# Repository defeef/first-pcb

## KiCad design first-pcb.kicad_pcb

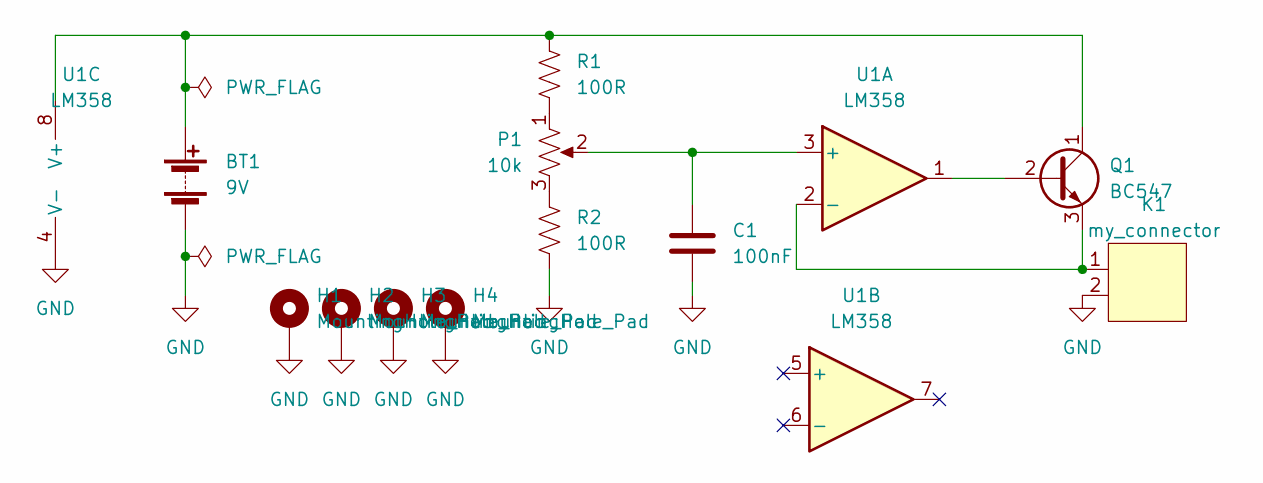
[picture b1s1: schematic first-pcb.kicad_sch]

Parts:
BT1: 9V; BatteryHolder_Eagle_12BH611-GR
C1: 100nF; C_Disc_D3.0mm_W2.0mm_P2.50mm
H1, H2, H3, H4: MountingHole_Pad; MountingHole_3.2mm_M3_Pad
K1: my_connector; PinHeader_1x02_P2.54mm_Vertical
P1: 10k; Potentiometer_Alps_RK09K_Single_Vertical
Q1: BC547; TO-92_Inline
R1, R2: 100R; R_Axial_DIN0207_L6.3mm_D2.5mm_P10.16mm_Horizontal
U1: LM358; DIP-8_W7.62mm

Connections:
GND: BT1.2 (-), C1.2, H1.1, H2.1, H3.1, H4.1, K1.2, R2.2, U1.4 (V-)
unnamed: BT1.1 (+), Q1.1 (C), R1.1, U1.8 (V+)
unnamed: C1.1, P1.2, U1.3 (+)
unnamed: K1.1, Q1.3 (E), U1.2 (-)
unnamed: P1.1, R1.2
unnamed: P1.3, R2.1
unnamed: Q1.2 (B), U1.1

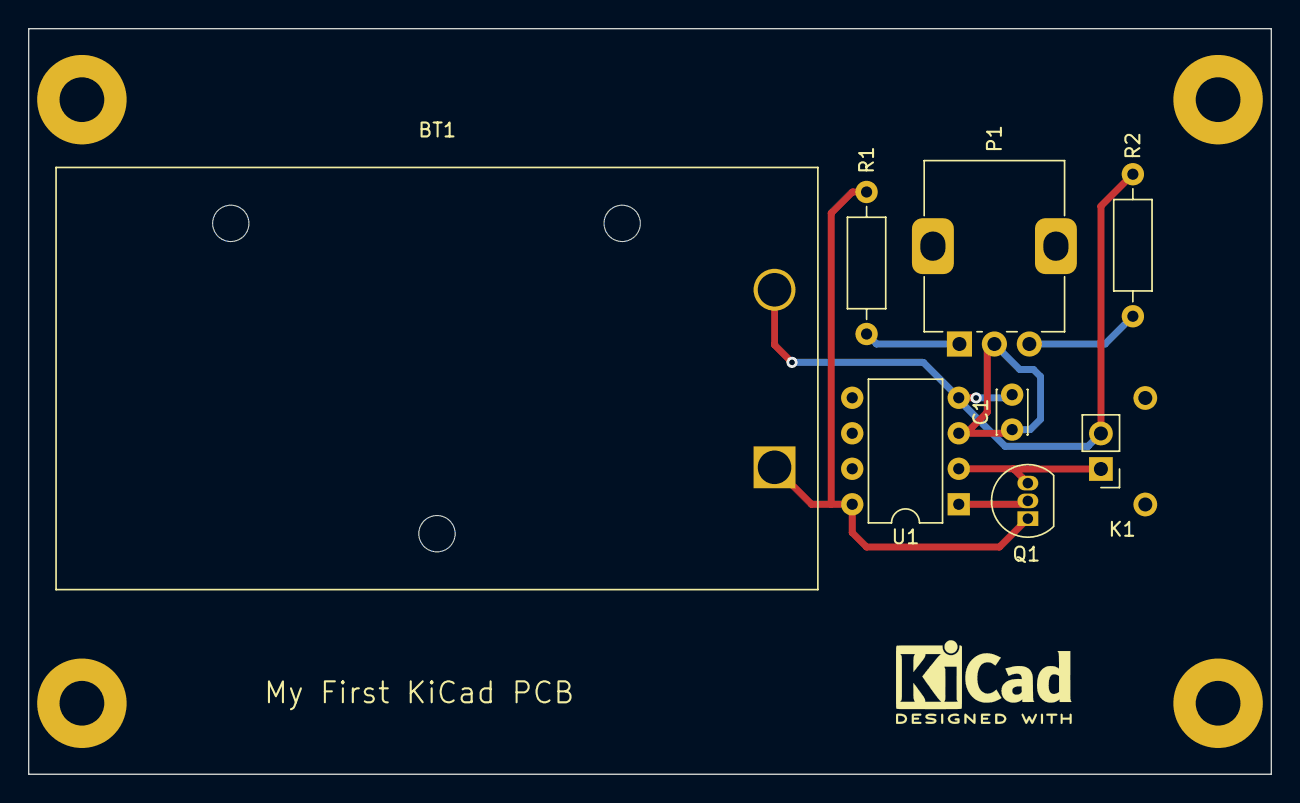
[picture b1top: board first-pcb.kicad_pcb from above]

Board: 2 copper layers, 88.9 x 53.3 mm, 12 parts (0 on the bottom side), 7 nets.

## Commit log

2022-06-07 Initialize project
2022-06-07 Add submodules
2022-06-07 Add footprint libraries
2022-06-08 Tutorial Switch
    Switching to a more broad schematic and pcb-making tutorial.
2022-06-08 Schematic Complete
2022-06-08 Pcb project setup
    Settings and constraints set for PCB Editor.
2022-06-08 Add Netlist
    Netlist imported to PCB Editor and placed, along with making board shape.
2022-06-08 Component Place
    Components from imported netlist are now organized better.
2022-06-08 Connector Footprint Update
    Added ground plane pins and resized the connector.
2022-06-08 Add Grounding Pins/Mounting Holes
2022-06-08 Adding Grounding Holes to pcb
2022-06-08 Back face/Bugfixing
2022-06-08 Routing
2022-06-08 Mounting Hole Footprint Change
    Changing mounting hole footprint to a pad to have the front and back connected.
2022-06-08 Dimensions/Silkscreen Icons/Text
2022-06-08 DRC Checks
2022-06-08 Production Files
2022-12-28 Backup
